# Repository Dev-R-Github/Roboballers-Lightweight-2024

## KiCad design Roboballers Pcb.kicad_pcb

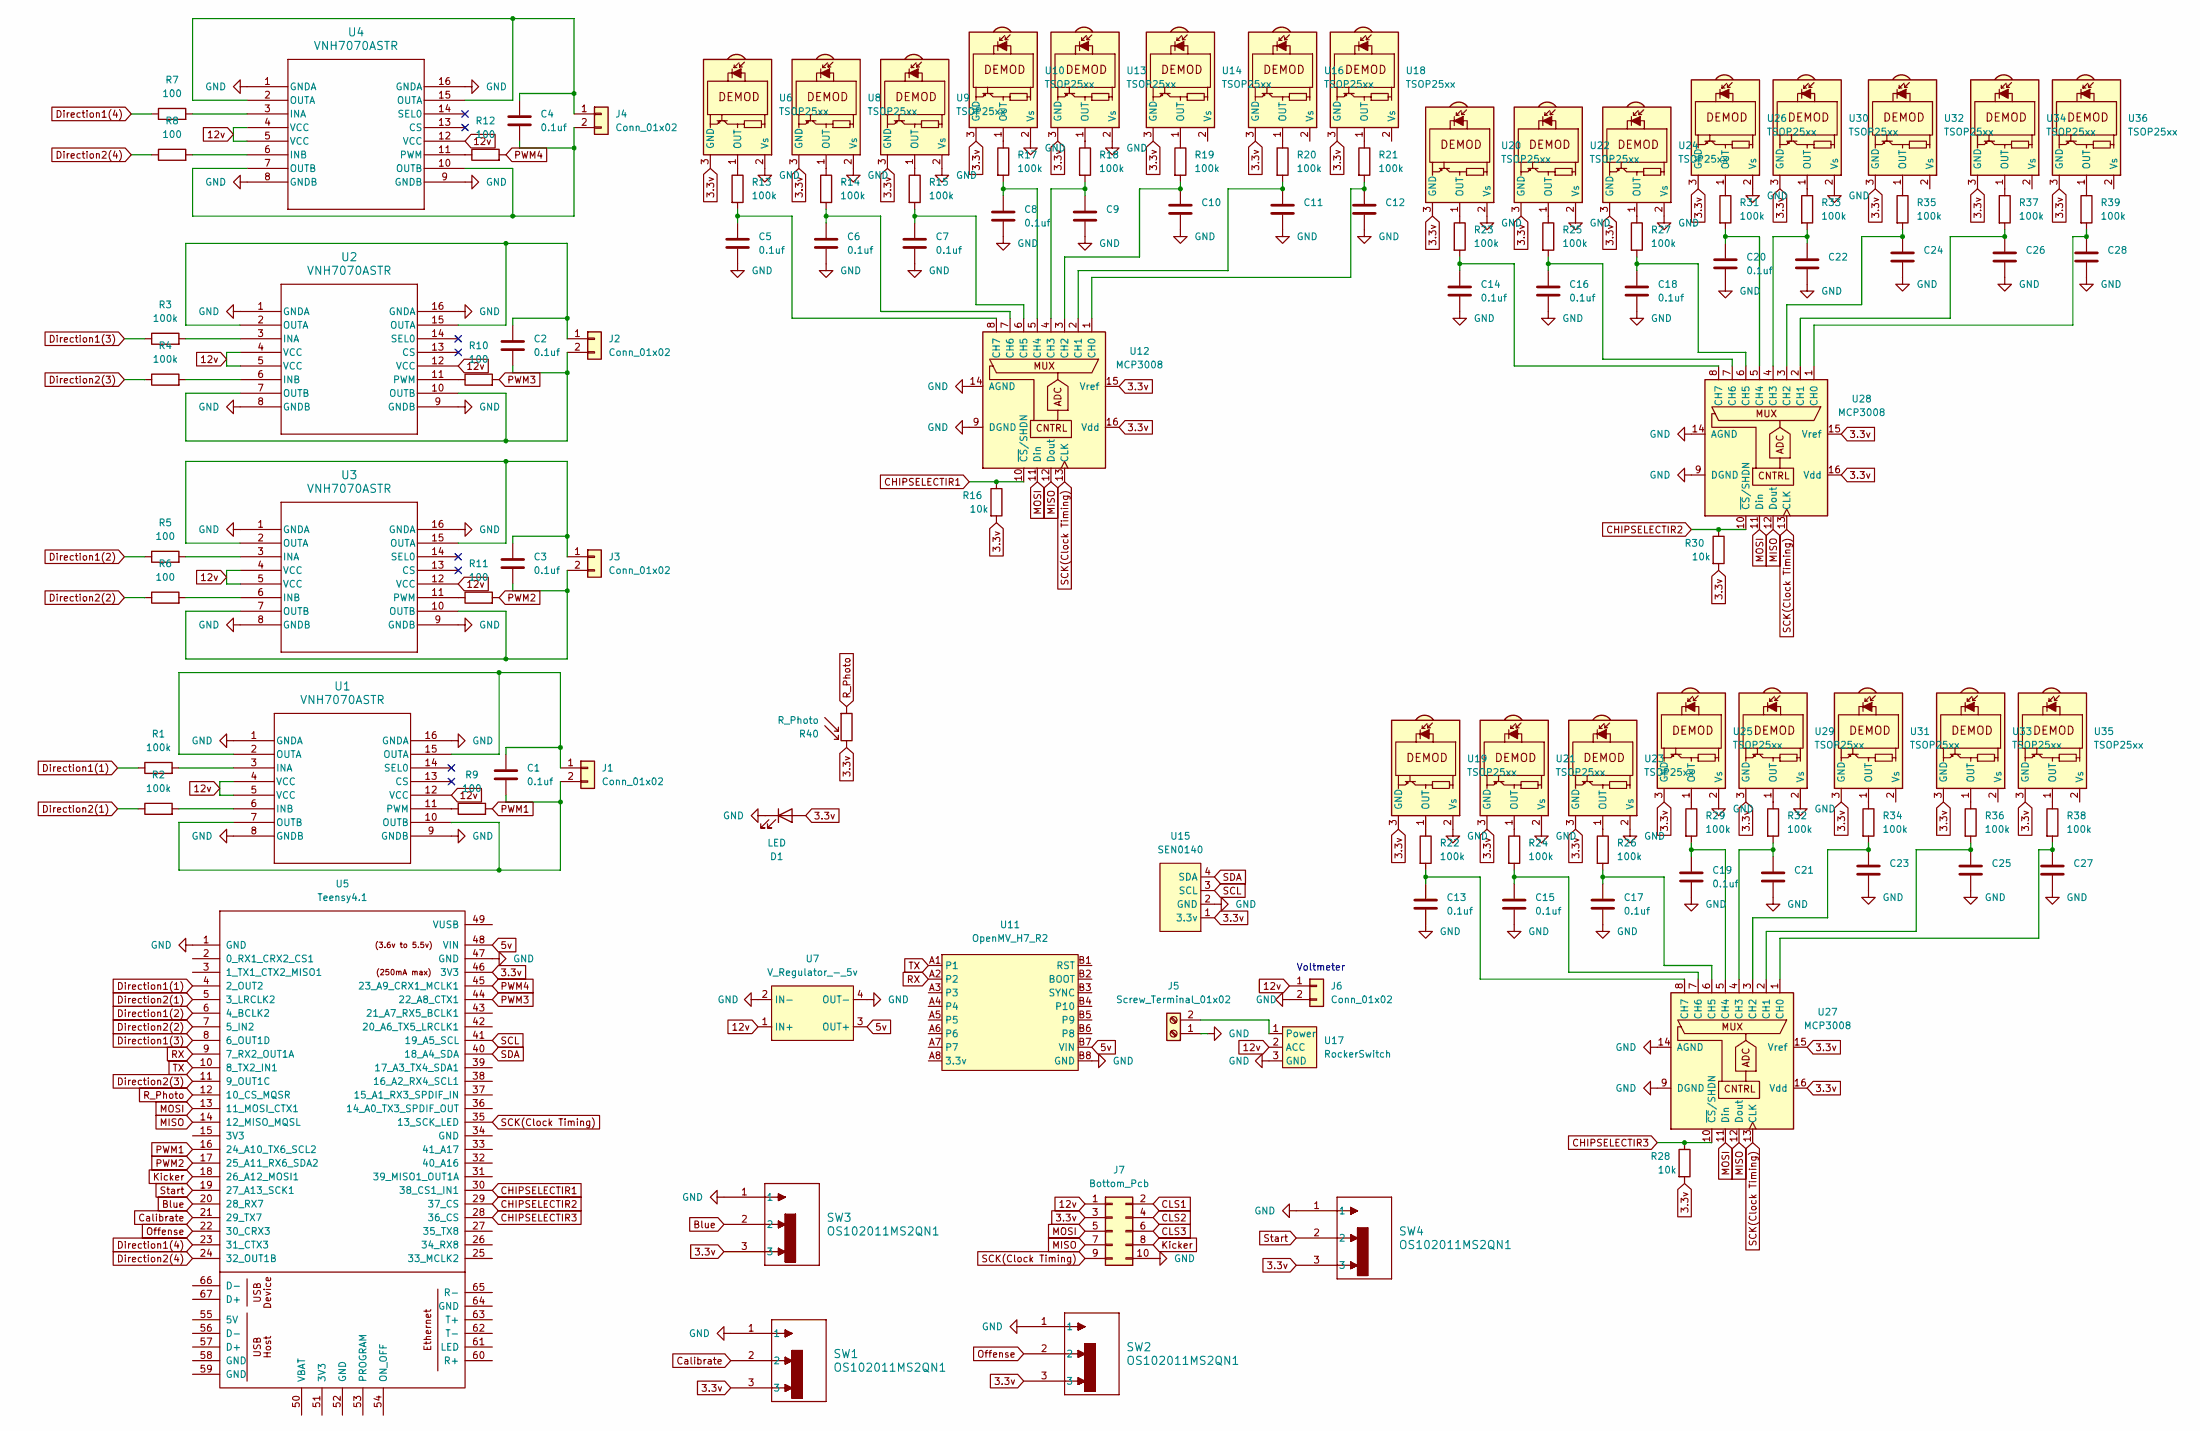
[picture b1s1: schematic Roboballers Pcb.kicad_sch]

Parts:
C1, C2, C3, C4, C5, C6, C7, C8, C9, C10, C11, C12, C13, C14, C15, C16, C17, C18, C19, C20, C21, C22, C23, C24, C25, C26, C27, C28: 0.1uf; C_0603_1608Metric_Pad1.08x0.95mm_HandSolder
D1: LED; LED_D1.8mm_W1.8mm_H2.4mm_Horizontal_O1.27mm_Z1.6mm
J1, J2, J3, J4: Conn_01x02; JST_XH_B2B-XH-AM_1x02_P2.50mm_Vertical
J5: Screw_Terminal_01x02; Pads
J6: Conn_01x02; PinHeader_1x02_P2.54mm_Vertical
J7: Bottom_Pcb; IDC-Header_2x05_P2.54mm_Vertical
R1, R2, R3, R4, R13, R14, R15, R17, R18, R19, R20, R21, R22, R23, R24, R25, R26, R27, R29, R31, R32, R33, R34, R35, R36, R37, R38, R39: 100k; R_0805_2012Metric_Pad1.20x1.40mm_HandSolder
R5, R6, R7, R8, R9, R10, R11, R12: 100; R_0805_2012Metric_Pad1.20x1.40mm_HandSolder
R16, R28, R30: 10k; R_0805_2012Metric_Pad1.20x1.40mm_HandSolder
R40: R_Photo; R_LDR_4.9x4.2mm_P2.54mm_Vertical
SW1, SW2, SW3, SW4: OS102011MS2QN1; SPDT_OS102011_CNK
U1, U2, U3, U4: VNH7070ASTR; SO-16N_STM-M
U5: Teensy4.1; Teensy41
U6, U8, U9, U10, U13, U14, U16, U18, U19, U20, U21, U22, U23, U24, U25, U26, U29, U30, U31, U32, U33, U34, U35, U36: TSOP25xx; TO_SP4038_VIS
U7: V_Regulator_-_5v; TerminalBlock_Phoenix_PT-1,5-4-5.0-H_1x04_P5.00mm_Horizontal
U11: OpenMV_H7_R2; OpenMV
U12, U27, U28: MCP3008; DIP-16_W7.62mm
U15: SEN0140; Compass Sensor DFRobot
U17: RockerSwitch; RF1-1A-DC-2-B-2

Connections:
3.3v: D1.2 (A), J7.3, R16.2, R28.2, R30.2, R40.2, SW1.3, SW2.3, SW3.3, SW4.3, U5.46 (3V3), U6.3 (GND), U8.3 (GND), U9.3 (GND), U10.3 (GND), U12.15 (Vref), U12.16 (Vdd), U13.3 (GND), U14.3 (GND), U15.1 (3.3v), U16.3 (GND), U18.3 (GND), U19.3 (GND), U20.3 (GND), U21.3 (GND), U22.3 (GND), U23.3 (GND), U24.3 (GND), U25.3 (GND), U26.3 (GND), U27.15 (Vref), U27.16 (Vdd), U28.15 (Vref), U28.16 (Vdd), U29.3 (GND), U30.3 (GND), U31.3 (GND), U32.3 (GND), U33.3 (GND), U34.3 (GND), U35.3 (GND), U36.3 (GND)
5v: U5.48 (VIN), U7.3 (OUT+), U11.B7 (VIN)
12v: J6.1, J7.1, U1.4 (VCC), U1.5 (VCC), U1.12 (VCC), U2.4 (VCC), U2.5 (VCC), U2.12 (VCC), U3.4 (VCC), U3.5 (VCC), U3.12 (VCC), U4.4 (VCC), U4.5 (VCC), U4.12 (VCC), U7.1 (IN+), U17.2 (ACC)
Blue: SW3.2, U5.20 (28_RX7)
CHIPSELECTIR1: R16.1, U5.30 (38_CS1_IN1), U12.10 (~CS/SHDN)
CHIPSELECTIR2: R30.1, U5.29 (37_CS), U28.10 (~CS/SHDN)
CHIPSELECTIR3: R28.1, U5.28 (36_CS), U27.10 (~CS/SHDN)
CLS1: J7.2, U5.25 (33_MCLK2)
CLS2: J7.4, U5.26 (34_RX8)
CLS3: J7.6, U5.27 (35_TX8)
Calibrate: SW1.2, U5.21 (29_TX7)
Direction1(1): R1.1, U5.4 (2_OUT2)
Direction1(2): R5.1, U5.6 (4_BCLK2)
Direction1(3): R3.1, U5.8 (6_OUT1D)
Direction1(4): R7.1, U5.23 (31_CTX3)
Direction2(1): R2.1, U5.5 (3_LRCLK2)
Direction2(2): R6.1, U5.7 (5_IN2)
Direction2(3): R4.1, U5.11 (9_OUT1C)
Direction2(4): R8.1, U5.24 (32_OUT1B)
GND: C5.2, C6.2, C7.2, C8.2, C9.2, C10.2, C11.2, C12.2, C13.2, C14.2, C15.2, C16.2, C17.2, C18.2, C19.2, C20.2, C21.2, C22.2, C23.2, C24.2, C25.2, C26.2, C27.2, C28.2, D1.1 (K), J5.1, J6.2, J7.10, SW1.1, SW2.1, SW3.1, SW4.1, U1.1 (GNDA), U1.8 (GNDB), U1.9 (GNDB), U1.16 (GNDA), U2.1 (GNDA), U2.8 (GNDB), U2.9 (GNDB), U2.16 (GNDA), U3.1 (GNDA), U3.8 (GNDB), U3.9 (GNDB), U3.16 (GNDA), U4.1 (GNDA), U4.8 (GNDB), U4.9 (GNDB), U4.16 (GNDA), U5.1 (GND), U5.47 (GND), U6.2 (Vs), U7.2 (IN-), U7.4 (OUT-), U8.2 (Vs), U9.2 (Vs), U10.2 (Vs), U11.B8 (GND), U12.9 (DGND), U12.14 (AGND), U13.2 (Vs), U15.2 (GND), U17.3 (GND), U19.2 (Vs), U20.2 (Vs), U21.2 (Vs), U22.2 (Vs), U23.2 (Vs), U24.2 (Vs), U25.2 (Vs), U26.2 (Vs), U27.9 (DGND), U27.14 (AGND), U28.9 (DGND), U28.14 (AGND), U29.2 (Vs), U30.2 (Vs)
Kicker: J7.8, U5.18 (26_A12_MOSI1)
MISO: J7.7, U5.14 (12_MISO_MQSL), U12.12 (Dout), U27.12 (Dout), U28.12 (Dout)
MOSI: J7.5, U5.13 (11_MOSI_CTX1), U12.11 (Din), U27.11 (Din), U28.11 (Din)
unnamed: C1.1, J1.1, U1.2 (OUTA), U1.15 (OUTA)
unnamed: C1.2, J1.2, U1.7 (OUTB), U1.10 (OUTB)
unnamed: C2.1, J2.1, U2.2 (OUTA), U2.15 (OUTA)
unnamed: C2.2, J2.2, U2.7 (OUTB), U2.10 (OUTB)
unnamed: C3.1, J3.1, U3.2 (OUTA), U3.15 (OUTA)
unnamed: C3.2, J3.2, U3.7 (OUTB), U3.10 (OUTB)
unnamed: C4.1, J4.1, U4.2 (OUTA), U4.15 (OUTA)
unnamed: C4.2, J4.2, U4.7 (OUTB), U4.10 (OUTB)
unnamed: J5.2, U17.1 (Power)
unnamed: R1.2, U1.3 (INA)
unnamed: R2.2, U1.6 (INB)
unnamed: R9.1, U1.11 (PWM)
unnamed: R3.2, U2.3 (INA)
unnamed: R4.2, U2.6 (INB)
unnamed: R10.1, U2.11 (PWM)
unnamed: R5.2, U3.3 (INA)
unnamed: R6.2, U3.6 (INB)
unnamed: R11.1, U3.11 (PWM)
unnamed: R7.2, U4.3 (INA)
unnamed: R8.2, U4.6 (INB)
unnamed: R12.1, U4.11 (PWM)
unnamed: R13.1, U6.1 (OUT)
unnamed: R14.1, U8.1 (OUT)
unnamed: R15.1, U9.1 (OUT)
unnamed: R17.1, U10.1 (OUT)
unnamed: C12.1, R21.2, U12.1 (CH0)
unnamed: C11.1, R20.2, U12.2 (CH1)
unnamed: C10.1, R19.2, U12.3 (CH2)
unnamed: C9.1, R18.2, U12.4 (CH3)
unnamed: C8.1, R17.2, U12.5 (CH4)
unnamed: C7.1, R15.2, U12.6 (CH5)
unnamed: C6.1, R14.2, U12.7 (CH6)
unnamed: C5.1, R13.2, U12.8 (CH7)
unnamed: R18.1, U13.1 (OUT)
unnamed: R19.1, U14.1 (OUT)
unnamed: R20.1, U16.1 (OUT)
unnamed: R21.1, U18.1 (OUT)
unnamed: R22.1, U19.1 (OUT)
unnamed: R23.1, U20.1 (OUT)
unnamed: R24.1, U21.1 (OUT)
unnamed: R25.1, U22.1 (OUT)
unnamed: R26.1, U23.1 (OUT)
unnamed: R27.1, U24.1 (OUT)
unnamed: R29.1, U25.1 (OUT)
unnamed: R31.1, U26.1 (OUT)
unnamed: C27.1, R38.2, U27.1 (CH0)
unnamed: C25.1, R36.2, U27.2 (CH1)
unnamed: C23.1, R34.2, U27.3 (CH2)
unnamed: C21.1, R32.2, U27.4 (CH3)
unnamed: C19.1, R29.2, U27.5 (CH4)
unnamed: C17.1, R26.2, U27.6 (CH5)
unnamed: C15.1, R24.2, U27.7 (CH6)
unnamed: C13.1, R22.2, U27.8 (CH7)
unnamed: C28.1, R39.2, U28.1 (CH0)
unnamed: C26.1, R37.2, U28.2 (CH1)
unnamed: C24.1, R35.2, U28.3 (CH2)
unnamed: C22.1, R33.2, U28.4 (CH3)
unnamed: C20.1, R31.2, U28.5 (CH4)
unnamed: C18.1, R27.2, U28.6 (CH5)
unnamed: C16.1, R25.2, U28.7 (CH6)
unnamed: C14.1, R23.2, U28.8 (CH7)
unnamed: R32.1, U29.1 (OUT)
unnamed: R33.1, U30.1 (OUT)
unnamed: R34.1, U31.1 (OUT)
unnamed: R35.1, U32.1 (OUT)
unnamed: R36.1, U33.1 (OUT)
unnamed: R37.1, U34.1 (OUT)
unnamed: R38.1, U35.1 (OUT)
unnamed: R39.1, U36.1 (OUT)
Offense: SW2.2, U5.22 (30_CRX3)
PWM1: R9.2, U5.16 (24_A10_TX6_SCL2)
PWM2: R11.2, U5.17 (25_A11_RX6_SDA2)
PWM3: R10.2, U5.44 (22_A8_CTX1)
PWM4: R12.2, U5.45 (23_A9_CRX1_MCLK1)
RX: U5.9 (7_RX2_OUT1A), U11.A2 (P2)
R_Photo: R40.1, U5.12 (10_CS_MQSR)
SCK(Clock Timing): J7.9, U5.35 (13_SCK_LED), U12.13 (CLK), U27.13 (CLK), U28.13 (CLK)
SCL: U5.41 (19_A5_SCL), U15.3 (SCL)
SDA: U5.40 (18_A4_SDA), U15.4 (SDA)
Start: SW4.2, U5.19 (27_A13_SCK1)
TX: U5.10 (8_TX2_IN1), U11.A1 (P1)

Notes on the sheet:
Voltmeter

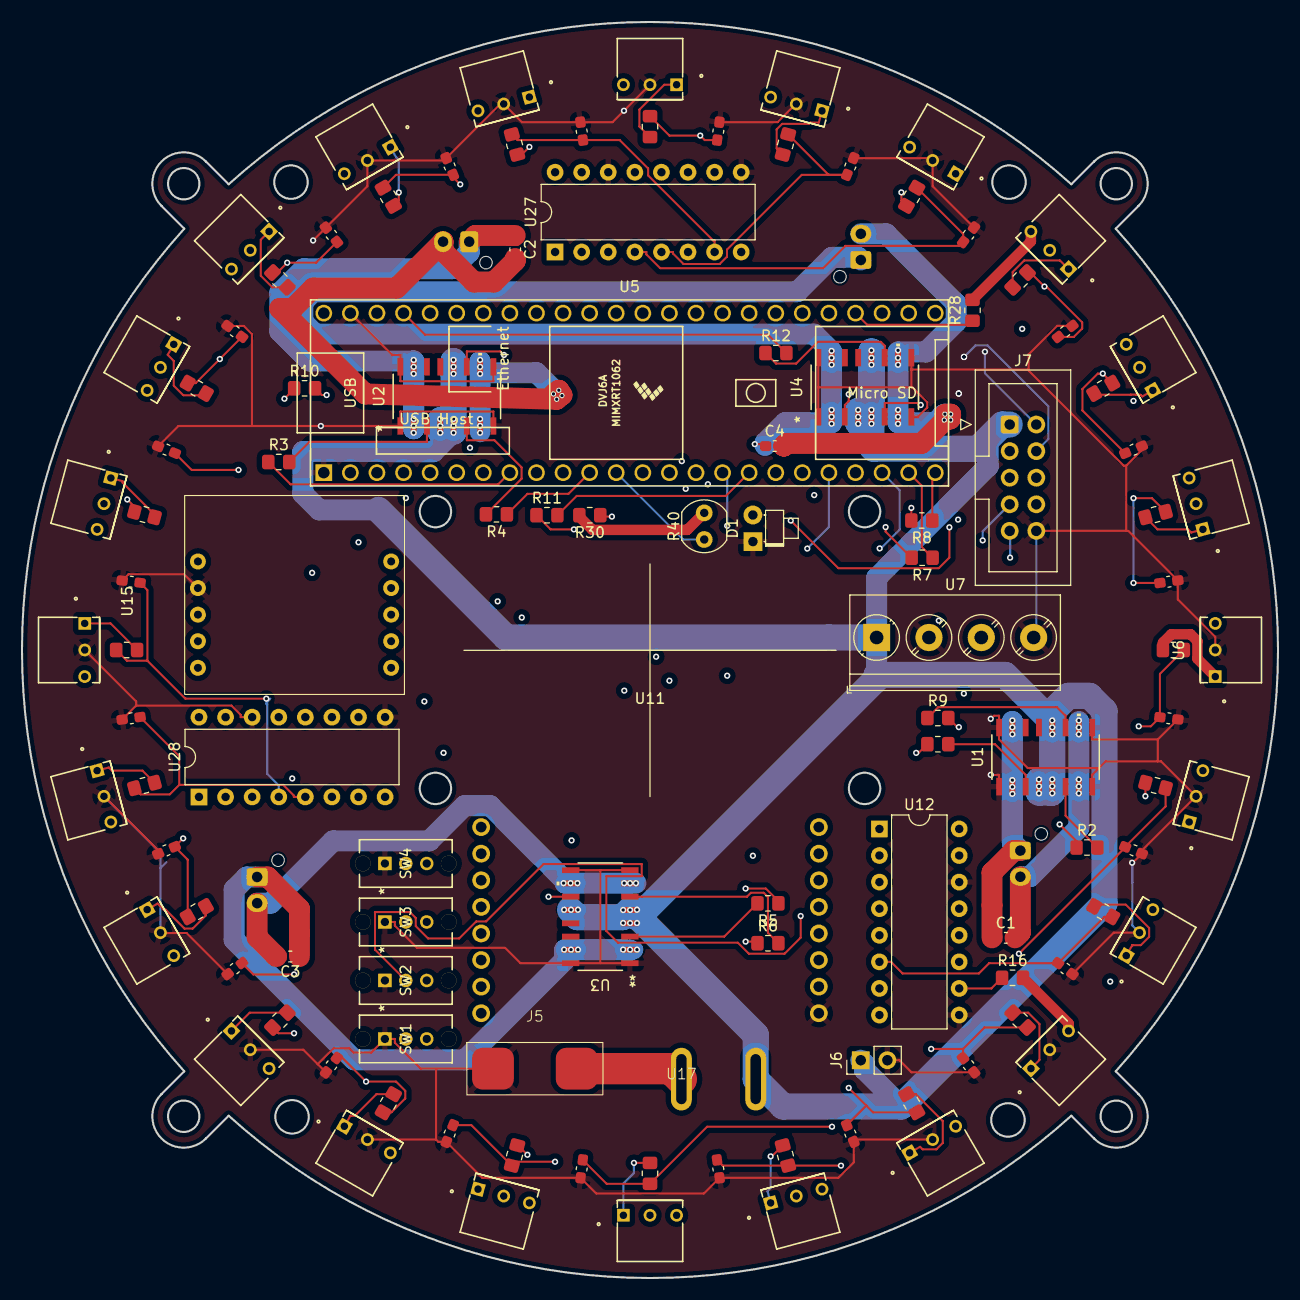
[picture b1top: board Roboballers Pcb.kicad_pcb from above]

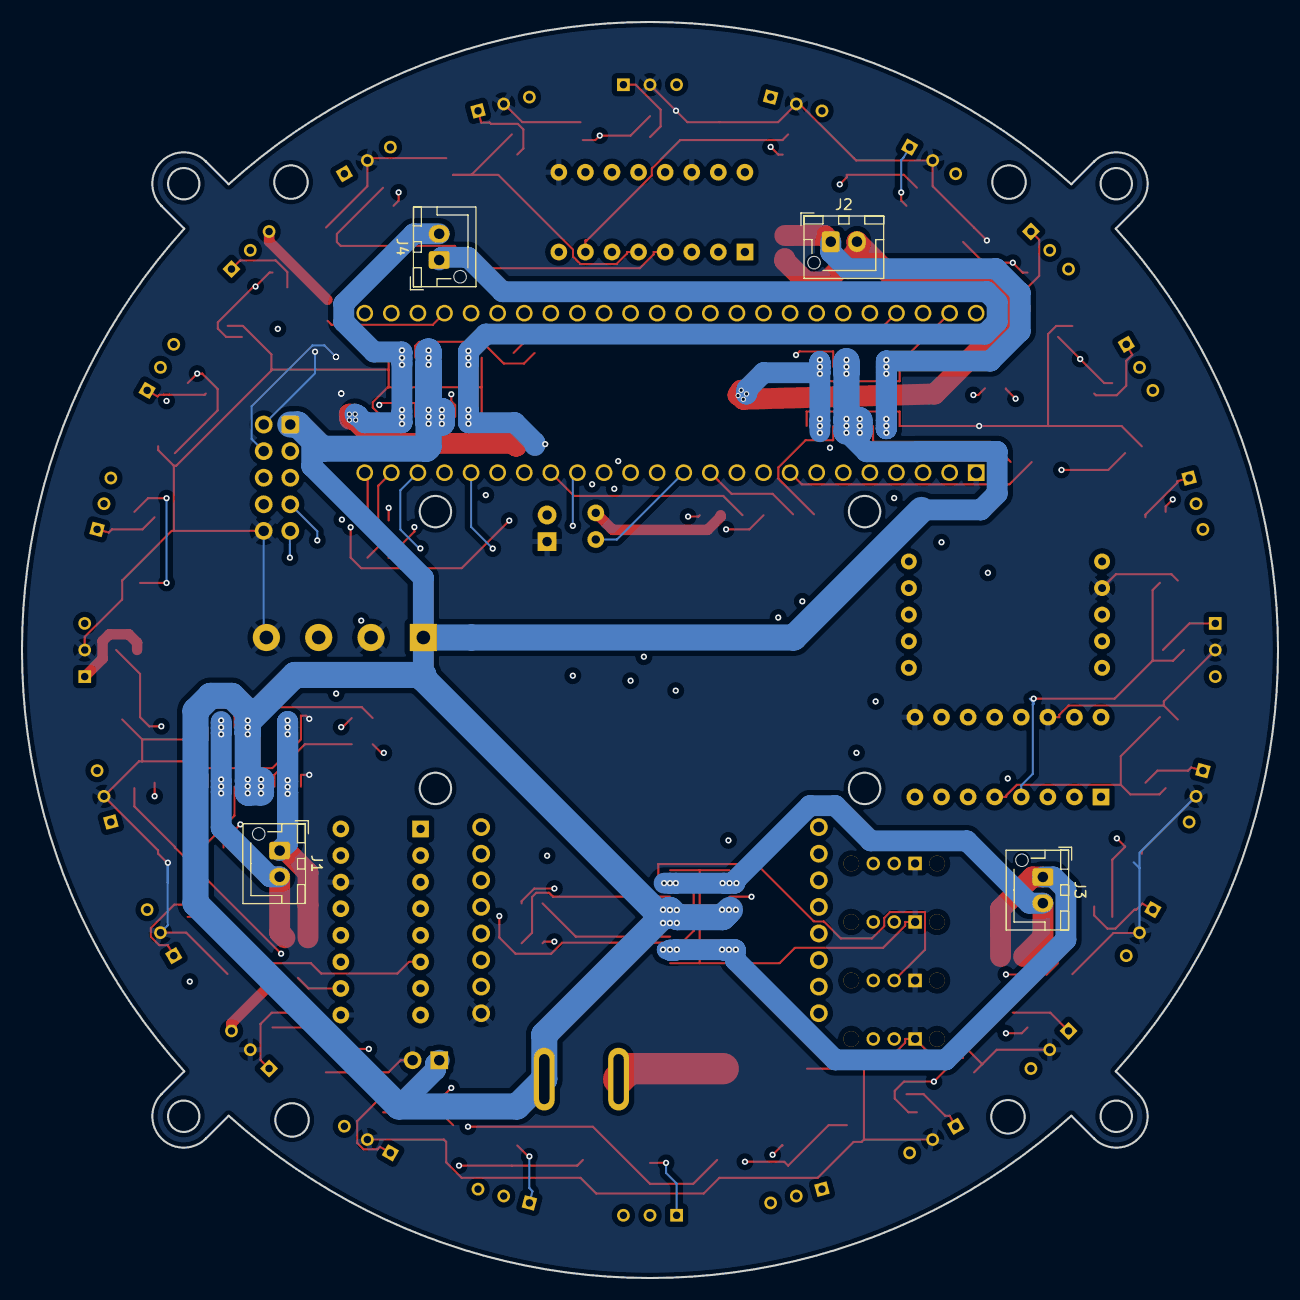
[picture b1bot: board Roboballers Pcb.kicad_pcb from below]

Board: 4 copper layers, 120.0 x 120.0 mm, 116 parts (4 on the bottom side), 104 nets.

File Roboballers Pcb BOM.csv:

"Reference","Value","Datasheet","Footprint","Qty","DNP"
"C1,C2,C3,C4,C5,C6,C7,C8,C9,C10,C11,C12,C13,C14,C15,C16,C17,C18,C19,C20,C21,C22,C23,C24,C25,C26,C27,C28","0.1uf","~","Capacitor_SMD:C_0603_1608Metric_Pad1.08x0.95mm_HandSolder","28",""
"D1","LED","~","LED_THT:LED_D1.8mm_W1.8mm_H2.4mm_Horizontal_O1.27mm_Z1.6mm","1",""
"J1,J2,J3,J4,J6","Conn_01x02","~","-- mixed values --","5",""
"J5","Screw_Terminal_01x02","~","Pads:Pads","1",""
"J7","Bottom_Pcb","~","Connector_IDC:IDC-Header_2x05_P2.54mm_Vertical","1",""
"R1,R2,R3,R4,R13,R14,R15,R17,R18,R19,R20,R21,R22,R23,R24,R25,R26,R27,R29,R31,R32,R33,R34,R35,R36,R37,R38,R39","100k","~","Resistor_SMD:R_0805_2012Metric_Pad1.20x1.40mm_HandSolder","28",""
"R5,R6,R7,R8,R9,R10,R11,R12","100","~","Resistor_SMD:R_0805_2012Metric_Pad1.20x1.40mm_HandSolder","8",""
"R16,R28,R30","10k","~","Resistor_SMD:R_0805_2012Metric_Pad1.20x1.40mm_HandSolder","3",""
"R40","R_Photo","~","OptoDevice:R_LDR_4.9x4.2mm_P2.54mm_Vertical","1",""
"SW1,SW2,SW3,SW4","OS102011MS2QN1","OS102011MS2QN1","os10..:SPDT_OS102011_CNK","4",""
"U1,U2,U3,U4","VNH7070ASTR","VNH7070ASTR","Vnh7070astr:SO-16N_STM-M","4",""
"U5","Teensy4.1","","teensy.pretty-master:Teensy41","1",""
"U6,U8,U9,U10,U13,U14,U16,U18,U19,U20,U21,U22,U23,U24,U25,U26,U29,U30,U31,U32,U33,U34,U35,U36","TSOP25xx","http://www.vishay.com/docs/82460/tsop45.pdf","ir sensor:TO_SP4038_VIS","24",""
"U7","V_Regulator_-_5v","","TerminalBlock_Phoenix:TerminalBlock_Phoenix_PT-1,5-4-5.0-H_1x04_P5.00mm_Horizontal","1",""
"U11","OpenMV_H7_R2","","Openmv:OpenMV","1",""
"U12,U27,U28","MCP3008","http://ww1.microchip.com/downloads/en/DeviceDoc/21295d.pdf","Package_DIP:DIP-16_W7.62mm","3",""
"U15","SEN0140","","Custom:Compass Sensor DFRobot","1",""
"U17","RockerSwitch","","RockerSwitch:RF1-1A-DC-2-B-2","1",""

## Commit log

2024-10-18 Testing
2024-10-18 Test
2024-10-18 Started on motor driver
2024-10-28 PS - MotorDriver Work
2024-11-15 Full pcb
2024-11-16 Added some Footprints
2024-11-17 i LOCKED TF IN
2024-11-20 good stuff
2024-11-21 nice
2024-11-29 nice stuff fixed all stuff
2024-11-30 I AM HIMMMMM
2024-11-30 i am him part 2
2024-12-03 idk what this is but i am pushing
2024-12-03 should be done now!!
2024-12-08 oh no 1 line sensor got cooked
2025-01-30 Schematic
    Added ground to sensors on schematic
2025-03-07 PS - fixed line cls connections
2025-04-25 PS - Final
